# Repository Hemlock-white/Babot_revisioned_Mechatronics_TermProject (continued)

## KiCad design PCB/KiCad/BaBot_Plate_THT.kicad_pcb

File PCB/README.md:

# BaBot through-hole conversion

The current Base is the fully routed **four-layer** `KiCad/BaBot_Base_THT_4067_Module.kicad_pro`; the current Plate is the routed **two-layer** `KiCad/BaBot_Plate_THT.kicad_pro`. The separate two-layer Base attempt is preserved under [`../history/PCB/base_2layer_draft/`](../history/PCB/base_2layer_draft/) and is **not ready to fabricate**: six signal connections and one GND connection remain open. The Plate's older unrouted board and rejected Gerbers are preserved under [`../history/PCB/`](../history/PCB/). Factory-assembled modules can still contain SMD parts.

See **[ROUTING.md](ROUTING.md)** for widths, clearances and current assumptions. The net classes and width presets are already configured in both projects.

Earlier learning notes are archived as [Base circuit learning guide](../history/notes/circuit_learning_base.md) and [Plate circuit learning guide](../history/notes/circuit_learning_plate.md). The illustrated [original](../docs/electronics_original.html) and [current THT](../docs/electronics_tht.html) lessons are in `docs/`.

## Files kept

`KiCad/` contains the routed Base and Plate projects, editable connection schematics, BOMs, connection tables, and the required local symbol/footprint libraries. Keep `BaBot_THT.pretty`, `BaBot_THT.kicad_sym`, `fp-lib-table` and `sym-lib-table` with the projects. `sources/` contains the two module schematic PDFs. `VALIDATION.md` records the handoff checks.

Fabrication files for the four-layer Base are in [`fabrication/BaBot_Base_THT_4layer/`](fabrication/BaBot_Base_THT_4layer/); the corrected two-layer Plate Gerbers and drills are in [`fabrication/plate_tht/`](fabrication/plate_tht/). Read each board's order notes before fabrication. The original Gerbers and BOMs remain under [`../original/pcbway/`](../original/pcbway/).

The Base and Plate CSV BOMs group identical purchase parts. `Qty per board` is for one board, and `Qty for 5 boards` is for five. Enter your stock in `Qty on hand` and change `[ ]` to `[x]` in `Have full 5-board qty?` when that complete five-board quantity is available. The Base BOM also counts cuttable socket strips, conditional module pin strips, and one Base–Plate cable per assembled pair; the cable is deliberately counted only once.

## Important assembly changes

- **Base U4:** assembled [Arduino Micro A000053](https://docs.arduino.cc/hardware/micro), using two 1×17 sockets on 2.54 mm pitch, rows 15.24 mm apart. This footprint is for the full Micro, not a Pro Micro. Its USB supplies logic and programming. MCU pin assignments were compared against Arduino's native CAD and the original board's manufacturing net data.
- **Base RV1:** [Bourns 3296W-1-104LF, 100 kΩ, 25-turn trimmer](https://www.lcsc.com/product-detail/C48084.html). Pad 1 receives `POT_H` from `R18`; pad 2 (wiper) and pad 3 go to GND. The old U2 DIGI POT 2 Click and J2 analog header are removed. With power off, measure between `RV1-1` and GND and adjust RV1 to about 10 kΩ as an initial setting; `R18` adds 500 Ω in series. Re-measure and tune using real sensor readings. A multi-turn adjustment can be turned in either direction.
- Use tall module sockets (approximately 8.5 mm or more clearance under the module) and trim opposite-side leads. Module body outlines are on F.Fab; the courtyards cover the socket strips. The Micro body overhangs the Base slightly. Confirm USB access, underside clearances, fastener access and fit with the printed mechanism; this is not a verified drop-in mechanical replacement.
- **Base U1:** CD74HC4067 16-channel through-hole breakout module. Check its two header rows and printed pin labels against the project footprint before ordering; the board maps the module pads to the IC's schematic pin numbers. The two-layer draft uses 1.7 mm copper pads around 0.8 mm drills (0.45 mm annular ring) to open routing space; the four-layer reference retains 2.0 mm pads. **Plate Q17:** FQP30N06L, TO-220; pin 1 gate, 2 drain, 3 source, with its tab also drain. The original MOSFET pin order was remapped. R23 adds a 220 Ω gate resistor; R22 remains a 10 kΩ gate pulldown.
- Base J1 is the new regulated **5 V servo/IR power input: pin 1 +5 V, pin 2 GND**. Logic and servo positive rails stay separate, with shared GND. Both supplies are needed for normal operation. This replaces the original dual USB-C/power-diode arrangement. The Micro provides the original MCU clock/reset/USB support and its onboard power indication.
- Base U3 and Plate U1 use matching **2×10, 2.54 mm headers**, connected with a straight-through 20-way cable, pin 1 to pin 1. Check orientation; these are unshrouded headers. Plate's header is on the underside. The original FPC cable will not fit.
- Original sensor/IR, servo-header and three mounting-hole positions are preserved. The Base perimeter was adjusted for copper-to-edge clearance and kept within a 99.95 mm width for the 100 × 100 mm fabrication price tier; check this small outline change against the enclosure. Plate resistors and Q17 are underneath; follow the BOM's F/B side column. IR204/H60 and 1540031NC6090 optical components retain the original pad mapping. Base U15 uses pin 1 cathode / pin 2 anode. Use 0.25 W axial resistors with 10.16 mm lead spacing; C1 is leaded 220 nF at 5 mm pitch, C5 is 10 µF/16 V at 2 mm pitch. Check the selected parts' dimensions against the footprints.

## Design basis and limits

The editable boards were reconstructed from the supplied Gerbers, BOMs and flying-probe nets because no original editable CAD was available. The connection schematics use generic passive-pin blocks, explicit pin numbers and net labels. They document connectivity and are linked to their PCB footprints; they are not functional ERC models or transistor-level schematics of the modules.

The later manufacturing BOM values were retained where the older schematic PDF disagreed: Plate R1–R21 = 330 Ω (PDF 500 Ω); Base R18 = 500 Ω (PDF 100 kΩ). The PDF's EEPROM circuitry was absent from the manufacturing BOM/probe data and was not added. These revision differences still need functional confirmation on the prototype. The current [`../software/main.ino`](../software/main.ino) is an unchanged copy of the available upstream firmware; that file contains no digital-pot startup command. Firmware behavior, operation, and mechanical fit have not been bench-tested with these PCBs.

Original robot design: [JohanLink/BABOT](https://github.com/JohanLink/BABOT). Module and trimmer references: [Arduino schematic](https://docs.arduino.cc/resources/schematics/A000053-schematics.pdf), [Bourns 3296 datasheet](https://www.bourns.com/docs/product-datasheets/3296.pdf). Keep the original design and vendor attribution/license terms when redistributing.

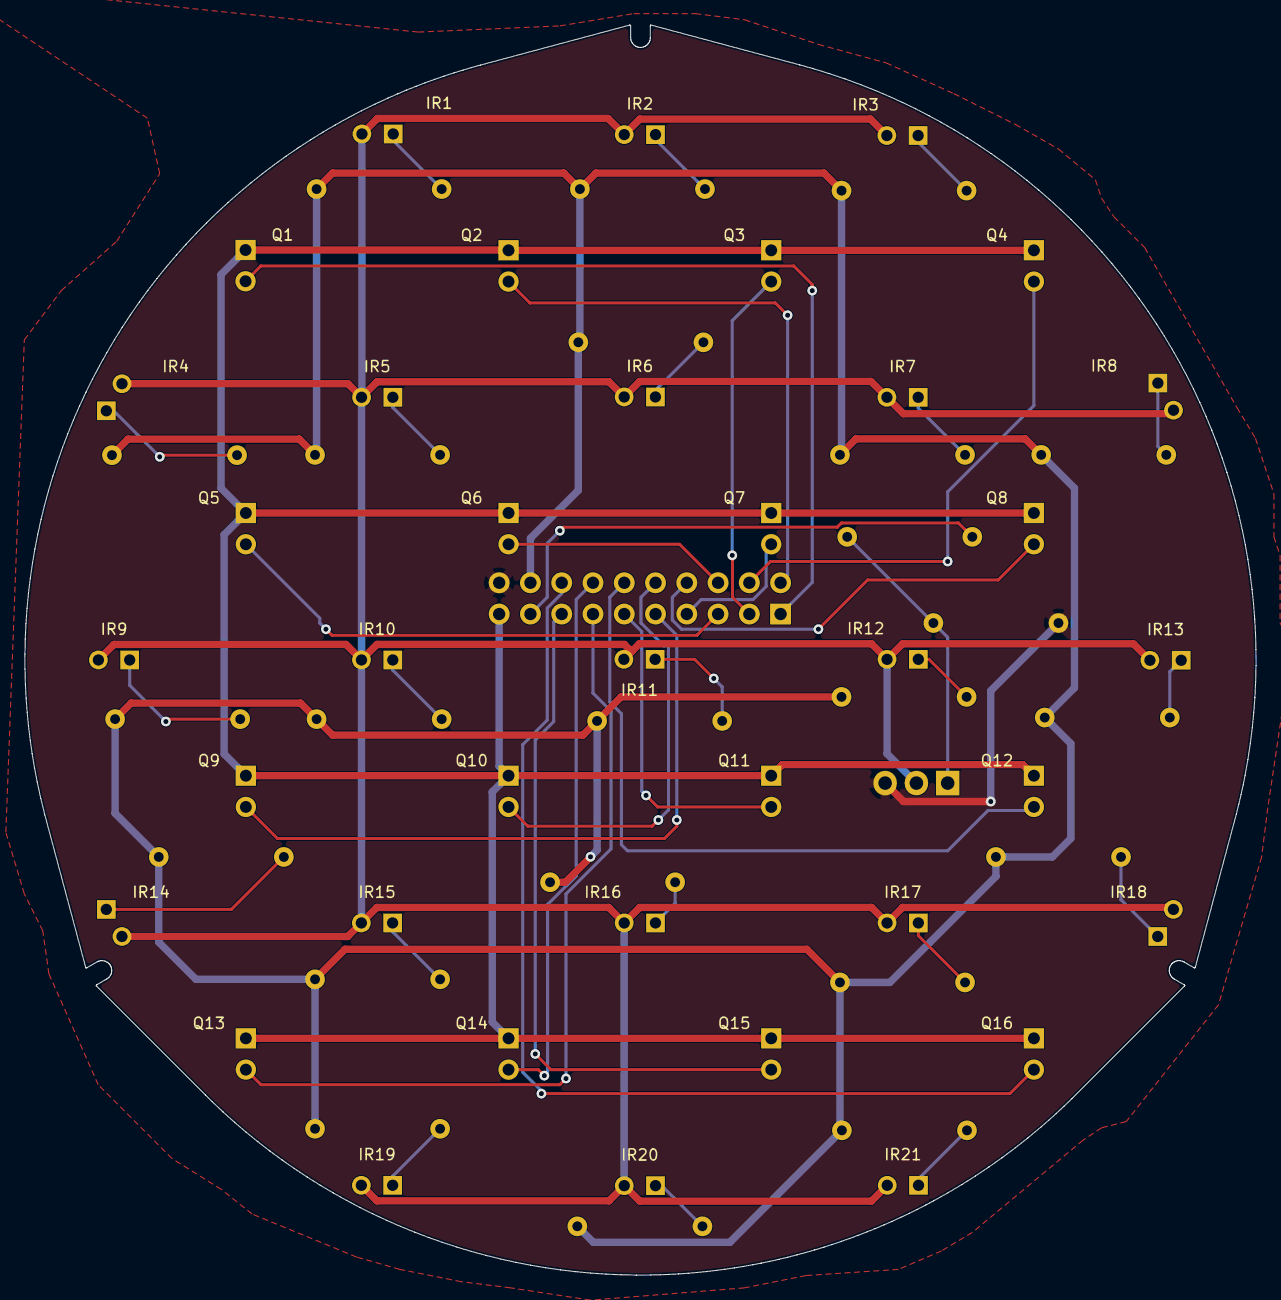
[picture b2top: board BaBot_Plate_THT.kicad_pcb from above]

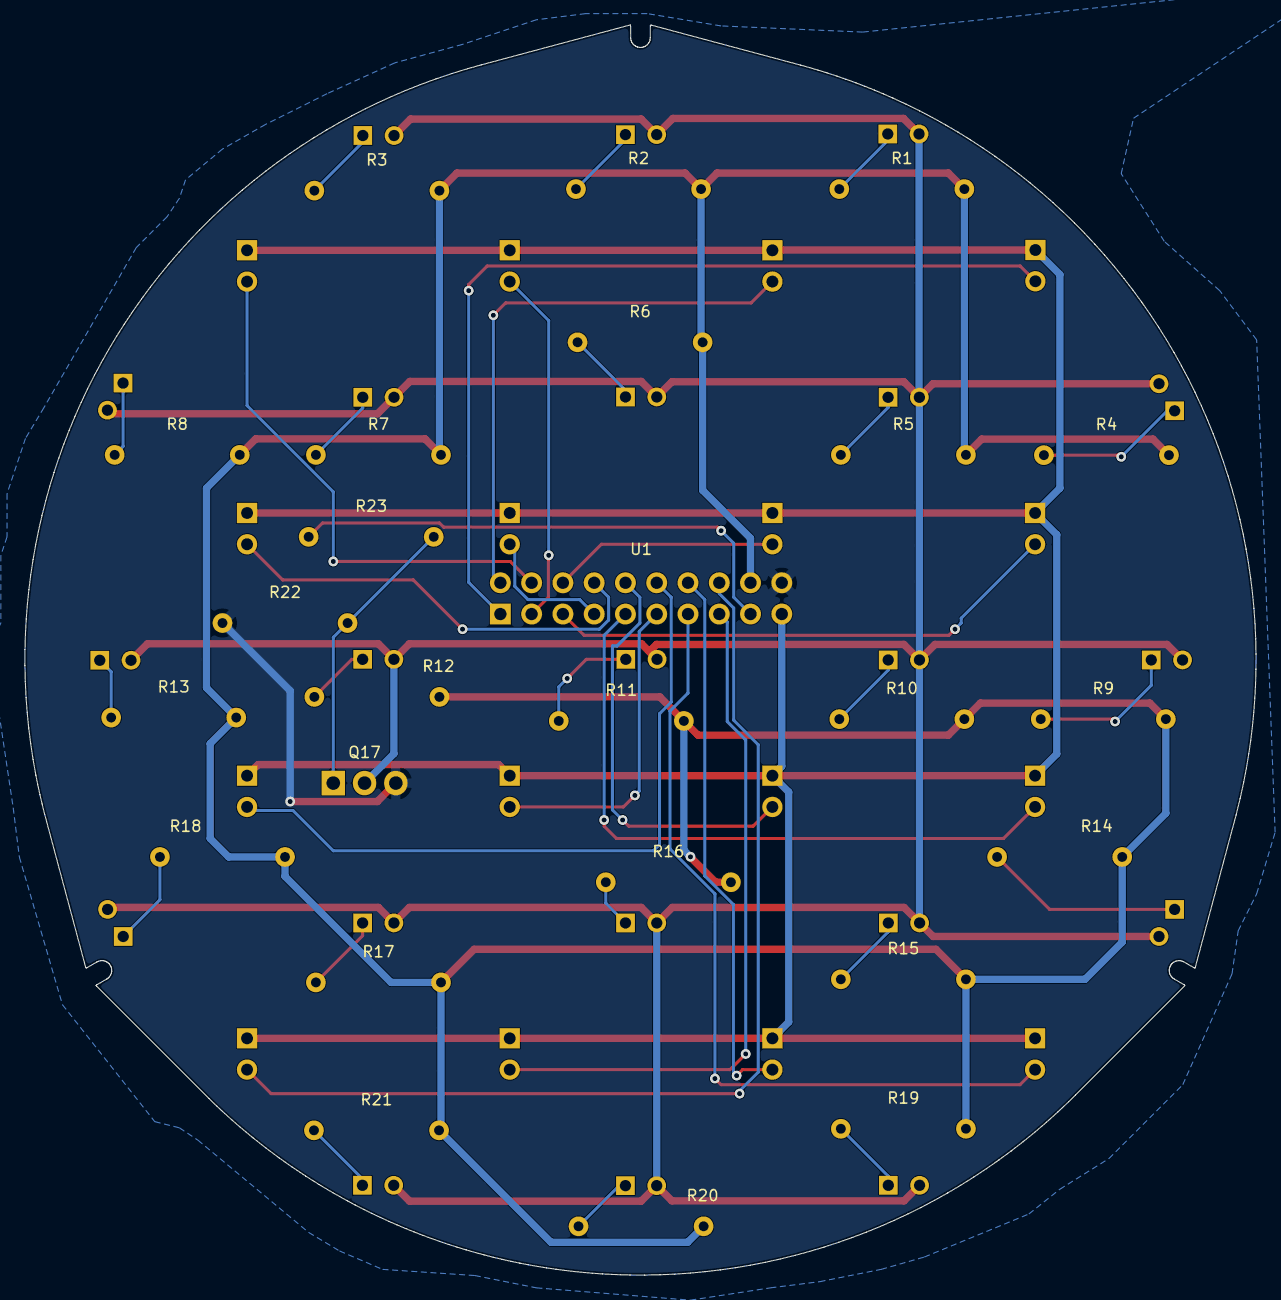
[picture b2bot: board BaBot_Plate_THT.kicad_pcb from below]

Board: 2 copper layers, 100.0 x 101.5 mm, 62 parts (25 on the bottom side), 43 nets.

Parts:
IR1: IR204/H60; Original_Plate_IR1
IR2: IR204/H60; Original_Plate_IR2
IR3: IR204/H60; Original_Plate_IR3
IR4: IR204/H60; Original_Plate_IR4
IR5: IR204/H60; Original_Plate_IR5
IR6: IR204/H60; Original_Plate_IR6
IR7: IR204/H60; Original_Plate_IR7
IR8: IR204/H60; Original_Plate_IR8
IR9: IR204/H60; Original_Plate_IR9
IR10: IR204/H60; Original_Plate_IR10
IR11: IR204/H60; Original_Plate_IR11
IR12: IR204/H60; Original_Plate_IR12
IR13: IR204/H60; Original_Plate_IR13
IR14: IR204/H60; Original_Plate_IR14
IR15: IR204/H60; Original_Plate_IR15
IR16: IR204/H60; Original_Plate_IR16
IR17: IR204/H60; Original_Plate_IR17
IR18: IR204/H60; Original_Plate_IR18
IR19: IR204/H60; Original_Plate_IR19
IR20: IR204/H60; Original_Plate_IR20
IR21: IR204/H60; Original_Plate_IR21
Q1: 1540031NC6090; Original_Plate_Q1
Q2: 1540031NC6090; Original_Plate_Q2
Q3: 1540031NC6090; Original_Plate_Q3
Q4: 1540031NC6090; Original_Plate_Q4
Q5: 1540031NC6090; Original_Plate_Q5
Q6: 1540031NC6090; Original_Plate_Q6
Q7: 1540031NC6090; Original_Plate_Q7
Q8: 1540031NC6090; Original_Plate_Q8
Q9: 1540031NC6090; Original_Plate_Q9
Q10: 1540031NC6090; Original_Plate_Q10
Q11: 1540031NC6090; Original_Plate_Q11
Q12: 1540031NC6090; Original_Plate_Q12
Q13: 1540031NC6090; Original_Plate_Q13
Q14: 1540031NC6090; Original_Plate_Q14
Q15: 1540031NC6090; Original_Plate_Q15
Q16: 1540031NC6090; Original_Plate_Q16
Q17: FQP30N06L; TO220_GDS
R1, R2, R3, R4, R5, R6, R7, R8, R9, R10, R11, R12, R13, R14, R15, R16, R17, R18, R19, R20, R21: 330; Axial_R_10.16
R22: 10k; Axial_R_10.16
R23: 220; Axial_R_10.16
U1: 20-way header to Base; Header20

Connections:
$1N2899: IR1.1, R1.1
$1N5933: IR2.1, R2.1
$1N6007: IR3.1, R3.1
$1N6081: IR4.1, R4.1
$1N6155: IR5.1, R5.1
$1N6229: IR6.1, R6.1
$1N6303: IR7.1, R7.1
$1N6377: IR8.1, R8.1
$1N6451: IR9.1, R9.1
$1N6525: IR10.1, R10.1
$1N6599: IR11.1, R11.1
$1N6673: IR12.1, R12.1
$1N6747: IR13.1, R13.1
$1N6821: IR14.1, R14.1
$1N6895: IR15.1, R15.1
$1N6969: IR16.1, R16.1
$1N7043: IR17.1, R17.1
$1N7117: IR18.1, R18.1
$1N7191: IR19.1, R19.1
$1N7265: IR20.1, R20.1
$1N7339: IR21.1, R21.1
+5V_LOGIC: Q1.1, Q2.1, Q3.1, Q4.1, Q5.1, Q6.1, Q7.1, Q8.1, Q9.1, Q10.1, Q11.1, Q12.1, Q13.1, Q14.1, Q15.1, Q16.1, U1.19
+5V_SERVO: R1.2, R2.2, R3.2, R4.2, R5.2, R6.2, R7.2, R8.2, R9.2, R10.2, R11.2, R12.2, R13.2, R14.2, R15.2, R16.2, R17.2, R18.2, R19.2, R20.2, R21.2, U1.18
GND: Q17.3, R22.1, U1.20
IR_CATHODES: IR1.2, IR2.2, IR3.2, IR4.2, IR5.2, IR6.2, IR7.2, IR8.2, IR9.2, IR10.2, IR11.2, IR12.2, IR13.2, IR14.2, IR15.2, IR16.2, IR17.2, IR18.2, IR19.2, IR20.2, IR21.2, Q17.2
IR_LED_CONTROL: R23.1, U1.17
MOSFET_GATE: Q17.1, R22.2, R23.2
PT00: Q1.2, U1.1
PT01: Q2.2, U1.2
PT02: Q3.2, U1.3
PT03: Q4.2, U1.4
PT04: Q5.2, U1.5
PT05: Q6.2, U1.6
PT06: Q7.2, U1.7
PT07: Q8.2, U1.8
PT08: Q9.2, U1.9
PT09: Q10.2, U1.10
PT10: Q11.2, U1.11
PT11: Q12.2, U1.12
PT12: Q13.2, U1.13
PT13: Q14.2, U1.14
PT14: Q15.2, U1.15
PT15: Q16.2, U1.16

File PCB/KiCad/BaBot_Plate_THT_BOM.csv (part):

Reference,Value,Footprint,Side,Purpose,Supplier Link
IR1,IR204/H60,Original_Plate_IR1,F,Original circuit; footprint converted or retained,https://www.lcsc.com/product-detail/C60099.html
IR2,IR204/H60,Original_Plate_IR2,F,Original circuit; footprint converted or retained,https://www.lcsc.com/product-detail/C60099.html
IR3,IR204/H60,Original_Plate_IR3,F,Original circuit; footprint converted or retained,https://www.lcsc.com/product-detail/C60099.html
IR4,IR204/H60,Original_Plate_IR4,F,Original circuit; footprint converted or retained,https://www.lcsc.com/product-detail/C60099.html
IR5,IR204/H60,Original_Plate_IR5,F,Original circuit; footprint converted or retained,https://www.lcsc.com/product-detail/C60099.html
IR6,IR204/H60,Original_Plate_IR6,F,Original circuit; footprint converted or retained,https://www.lcsc.com/product-detail/C60099.html
IR7,IR204/H60,Original_Plate_IR7,F,Original circuit; footprint converted or retained,https://www.lcsc.com/product-detail/C60099.html
IR8,IR204/H60,Original_Plate_IR8,F,Original circuit; footprint converted or retained,https://www.lcsc.com/product-detail/C60099.html
IR9,IR204/H60,Original_Plate_IR9,F,Original circuit; footprint converted or retained,https://www.lcsc.com/product-detail/C60099.html
IR10,IR204/H60,Original_Plate_IR10,F,Original circuit; footprint converted or retained,https://www.lcsc.com/product-detail/C60099.html
IR11,IR204/H60,Original_Plate_IR11,F,Original circuit; footprint converted or retained,https://www.lcsc.com/product-detail/C60099.html
IR12,IR204/H60,Original_Plate_IR12,F,Original circuit; footprint converted or retained,https://www.lcsc.com/product-detail/C60099.html
IR13,IR204/H60,Original_Plate_IR13,F,Original circuit; footprint converted or retained,https://www.lcsc.com/product-detail/C60099.html
IR14,IR204/H60,Original_Plate_IR14,F,Original circuit; footprint converted or retained,https://www.lcsc.com/product-detail/C60099.html
IR15,IR204/H60,Original_Plate_IR15,F,Original circuit; footprint converted or retained,https://www.lcsc.com/product-detail/C60099.html
IR16,IR204/H60,Original_Plate_IR16,F,Original circuit; footprint converted or retained,https://www.lcsc.com/product-detail/C60099.html
IR17,IR204/H60,Original_Plate_IR17,F,Original circuit; footprint converted or retained,https://www.lcsc.com/product-detail/C60099.html
IR18,IR204/H60,Original_Plate_IR18,F,Original circuit; footprint converted or retained,https://www.lcsc.com/product-detail/C60099.html
IR19,IR204/H60,Original_Plate_IR19,F,Original circuit; footprint converted or retained,https://www.lcsc.com/product-detail/C60099.html
IR20,IR204/H60,Original_Plate_IR20,F,Original circuit; footprint converted or retained,https://www.lcsc.com/product-detail/C60099.html
IR21,IR204/H60,Original_Plate_IR21,F,Original circuit; footprint converted or retained,https://www.lcsc.com/product-detail/C60099.html
Q1,1540031NC6090,Original_Plate_Q1,F,Original circuit; footprint converted or retained,https://shopee.tw/search?keyword=Wurth%20Elektronik%20154003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
Q2,1540031NC6090,Original_Plate_Q2,F,Original circuit; footprint converted or retained,https://shopee.tw/search?keyword=Wurth%20Elektronik%20154003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
Q3,1540031NC6090,Original_Plate_Q3,F,Original circuit; footprint converted or retained,https://shopee.tw/search?keyword=Wurth%20Elektronik%20154003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
Q4,1540031NC6090,Original_Plate_Q4,F,Original circuit; footprint converted or retained,https://shopee.tw/search?keyword=Wurth%20Elektronik%20154003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
Q5,1540031NC6090,Original_Plate_Q5,F,Original circuit; footprint converted or retained,https://shopee.tw/search?keyword=Wurth%20Elektronik%20154003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
Q6,1540031NC6090,Original_Plate_Q6,F,Original circuit; footprint converted or retained,https://shopee.tw/search?keyword=Wurth%20Elektronik%20154003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
Q7,1540031NC6090,Original_Plate_Q7,F,Original circuit; footprint converted or retained,https://shopee.tw/search?keyword=Wurth%20Elektronik%20154003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
Q8,1540031NC6090,Original_Plate_Q8,F,Original circuit; footprint converted or retained,https://shopee.tw/search?keyword=Wurth%20Elektronik%20154003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
Q9,1540031NC6090,Original_Plate_Q9,F,Original circuit; footprint converted or retained,https://shopee.tw/search?keyword=Wurth%20Elektronik%20154003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
Q10,1540031NC6090,Original_Plate_Q10,F,Original circuit; footprint converted or retained,https://shopee.tw/search?keyword=Wurth%20Elektronik%20154003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
Q11,1540031NC6090,Original_Plate_Q11,F,Original circuit; footprint converted or retained,https://shopee.tw/search?keyword=Wurth%20Elektronik%20154003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
Q12,1540031NC6090,Original_Plate_Q12,F,Original circuit; footprint converted or retained,https://shopee.tw/search?keyword=Wurth%20Elektronik%20154003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
Q13,1540031NC6090,Original_Plate_Q13,F,Original circuit; footprint converted or retained,https://shopee.tw/search?keyword=Wurth%20Elektronik%20154003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
Q14,1540031NC6090,Original_Plate_Q14,F,Original circuit; footprint converted or retained,https://shopee.tw/search?keyword=Wurth%20Elektronik%20154003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
Q15,1540031NC6090,Original_Plate_Q15,F,Original circuit; footprint converted or retained,https://shopee.tw/search?keyword=Wurth%20Elektronik%20154003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
Q16,1540031NC6090,Original_Plate_Q16,F,Original circuit; footprint converted or retained,https://shopee.tw/search?keyword=Wurth%20Elektronik%20154003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
R1,330,Axial_R_10.16,B,Original circuit; footprint converted or retained,https://www.lcsc.com/product-detail/C2894590.html
R2,330,Axial_R_10.16,B,Original circuit; footprint converted or retained,https://www.lcsc.com/product-detail/C2894590.html
R3,330,Axial_R_10.16,B,Original circuit; footprint converted or retained,https://www.lcsc.com/product-detail/C2894590.html
R4,330,Axial_R_10.16,B,Original circuit; footprint converted or retained,https://www.lcsc.com/product-detail/C2894590.html
R5,330,Axial_R_10.16,B,Original circuit; footprint converted or retained,https://www.lcsc.com/product-detail/C2894590.html
R6,330,Axial_R_10.16,B,Original circuit; footprint converted or retained,https://www.lcsc.com/product-detail/C2894590.html
R7,330,Axial_R_10.16,B,Original circuit; footprint converted or retained,https://www.lcsc.com/product-detail/C2894590.html
R8,330,Axial_R_10.16,B,Original circuit; footprint converted or retained,https://www.lcsc.com/product-detail/C2894590.html
R9,330,Axial_R_10.16,B,Original circuit; footprint converted or retained,https://www.lcsc.com/product-detail/C2894590.html
R10,330,Axial_R_10.16,B,Original circuit; footprint converted or retained,https://www.lcsc.com/product-detail/C2894590.html
R11,330,Axial_R_10.16,B,Original circuit; footprint converted or retained,https://www.lcsc.com/product-detail/C2894590.html
R12,330,Axial_R_10.16,B,Original circuit; footprint converted or retained,https://www.lcsc.com/product-detail/C2894590.html
R13,330,Axial_R_10.16,B,Original circuit; footprint converted or retained,https://www.lcsc.com/product-detail/C2894590.html
R14,330,Axial_R_10.16,B,Original circuit; footprint converted or retained,https://www.lcsc.com/product-detail/C2894590.html
R15,330,Axial_R_10.16,B,Original circuit; footprint converted or retained,https://www.lcsc.com/product-detail/C2894590.html
R16,330,Axial_R_10.16,B,Original circuit; footprint converted or retained,https://www.lcsc.com/product-detail/C2894590.html
R17,330,Axial_R_10.16,B,Original circuit; footprint converted or retained,https://www.lcsc.com/product-detail/C2894590.html
R18,330,Axial_R_10.16,B,Original circuit; footprint converted or retained,https://www.lcsc.com/product-detail/C2894590.html
R19,330,Axial_R_10.16,B,Original circuit; footprint converted or retained,https://www.lcsc.com/product-detail/C2894590.html
R20,330,Axial_R_10.16,B,Original circuit; footprint converted or retained,https://www.lcsc.com/product-detail/C2894590.html
R21,330,Axial_R_10.16,B,Original circuit; footprint converted or retained,https://www.lcsc.com/product-detail/C2894590.html
U1,20-way header to Base,Header20,B,Original circuit; footprint converted or retained,https://www.lcsc.com/product-detail/C54803349.html
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
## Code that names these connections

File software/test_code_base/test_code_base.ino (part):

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const uint8_t PIN_BUTTON = A1;       // SW1 + 外部下拉 R7：放開 LOW，按下 HIGH
const uint8_t PIN_BOARD_LED = 8;     // U15 + 限流 R10：HIGH 亮，LOW 滅
const uint8_t PIN_IR_CONTROL = 7;    // U3-17；沒有 Plate 時只測控制訊號
const uint8_t PIN_MUX_SIGNAL = A0;   // U1_SIG；讀取選到的 PT00~PT15
const uint8_t PIN_MUX_SELECT[4] = {5, 13, 6, 12}; // S0,S1,S2,S3
const uint8_t PIN_SERVO[3] = {11, 10, 9};         // H1/H2/H3 訊號腳

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
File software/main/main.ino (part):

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  pinMode(LED_PIN,         OUTPUT);
  pinMode(IR_LED_PIN,      OUTPUT);

  servoA.attach(SERVO_PIN_A);
  servoB.attach(SERVO_PIN_B);
  servoC.attach(SERVO_PIN_C);

  // EEPROM calibration is intentionally bypassed for this test. The global
  // servoOffsetA/B/C defaults (100) apply, independent of old EEPROM data.
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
